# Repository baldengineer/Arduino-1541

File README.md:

# Arduino-1541
Interact with a Commodore 1541 from an Arduino

## Streaming notes
This project was created as a part of a [Bald Engineer Live Stream](https://twitch.tv/baldengineer). For stream-by-stream notes, [check out this repo](https://bald.ee/60-notes).

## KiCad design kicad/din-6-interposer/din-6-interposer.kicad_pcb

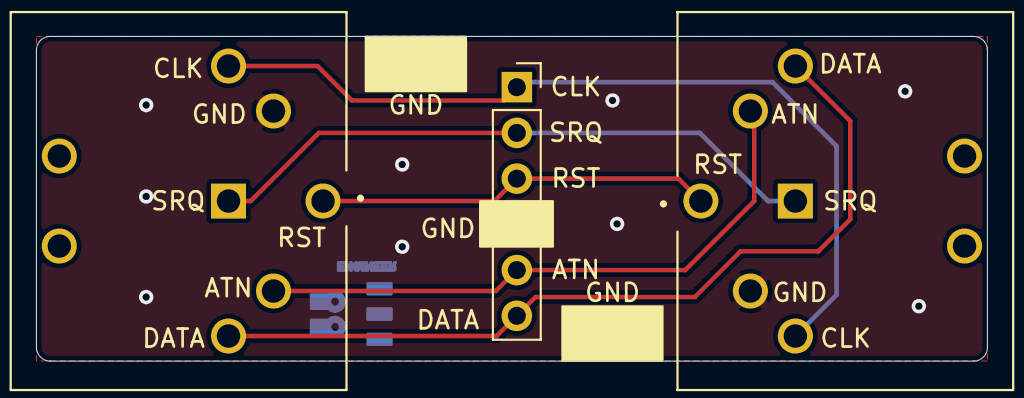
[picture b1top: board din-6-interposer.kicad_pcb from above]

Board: 2 copper layers, 52.8 x 18.0 mm, 6 parts (1 on the bottom side), 6 nets.

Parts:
J1: LA; PinSocket_1x06_P2.54mm_Vertical
J2: IN; CUI_SDF-60J
J3: OUT; CUI_SDF-60J
TP1, TP2: GND; Harwin-S1751-46-Test-Point
svg2mod: G***; BE5v2

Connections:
/ATN: J1.5, J2.3, J3.3
/CLK: J1.1, J2.4, J3.4
/DATA: J1.6, J2.5, J3.5
/RESET: J1.3, J2.6, J3.6
/SRQ: J1.2, J2.1, J3.1
GND: J1.4, J2.2, J3.2, TP1.1, TP2.1

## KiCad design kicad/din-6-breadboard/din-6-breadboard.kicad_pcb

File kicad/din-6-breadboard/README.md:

## DIN 6 (IEC / CBM Bus) Adapter to Breadboard

Contains level shifter to communicate between 3v3 and 5v Arduino boards.

## Streaming notes
This project was created as a part of a [Bald Engineer Live Stream](https://twitch.tv/baldengineer). For stream-by-stream notes, [check out this repo](https://bald.ee/60-notes).

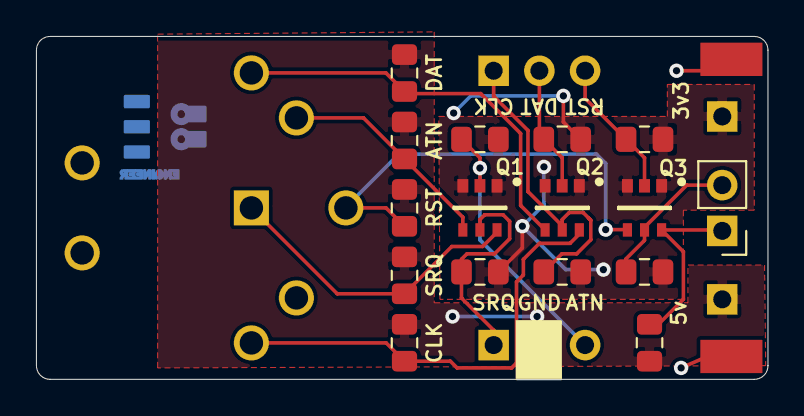
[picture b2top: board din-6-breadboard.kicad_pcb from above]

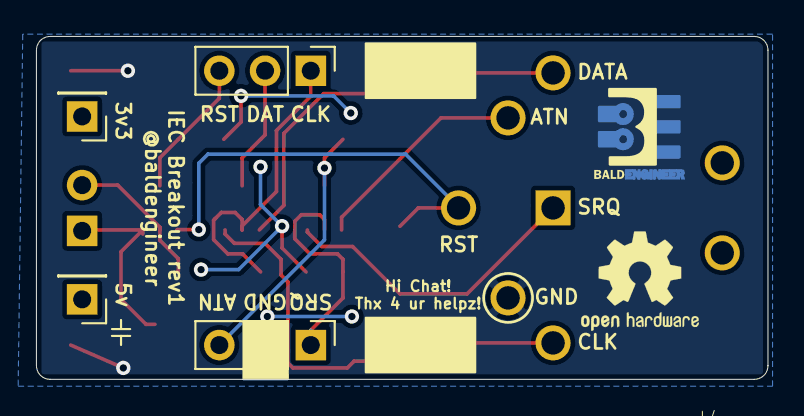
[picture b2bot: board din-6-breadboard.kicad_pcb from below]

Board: 2 copper layers, 40.6 x 19.0 mm, 24 parts (6 on the bottom side), 15 nets.

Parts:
J1, J2: Conn_01x03; PinHeader_1x03_P2.54mm_Vertical
J3: Conn_01x02; PinHeader_1x02_P2.54mm_Vertical
J4: IN; CUI_SDF-60J
J5: 3v3; PinHeader_1x01_P2.54mm_Vertical
J6: 5v; PinHeader_1x01_P2.54mm_Vertical
Q1, Q2, Q3: FDC6301N; ON_Semi-419AG-01-0-0-0
R1, R2, R3, R4, R5, R6, R7, R8, R9, R10, R11, R12: 4k7; R_0805_2012Metric_Pad1.15x1.40mm_HandSolder
TP1, TP2: GND; Harwin-S1751-46-Test-Point
svg2mod: G***; BE5v2

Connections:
+3V3: J5.1, Q1.1, Q1.3, Q2.1, Q2.3, Q3.1, Q3.3, R1.2, R3.2, R5.2, R7.2, R9.2, R11.2
+5V: J6.1, R2.2, R4.2, R6.2, R8.2, R10.2, R12.2
/ATN3: J1.3, Q1.2, R3.1
/ATN5: J4.3, Q1.4, R4.1
/CLK3: J2.1, Q2.5, R5.1
/CLK5: J4.4, Q2.6, R6.1
/DATA3: J2.2, Q2.2, R7.1
/DATA5: J4.5, Q2.4, R8.1
/RESET3: J2.3, Q3.2, R9.1
/RESET5: J4.6, Q3.4, R10.1
/SRQ3: J1.1, Q1.5, R1.1
/SRQ5: J4.1, Q1.6, R2.1
/Spare_Aux_H: J3.1, Q3.6, R12.1
/Spare_Aux_L: J3.2, Q3.5, R11.1
GND: J1.2, J4.2, TP1.1, TP2.1

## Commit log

2021-03-14 pre-routing
2021-03-14 pre-flood 3v and 5v
2021-03-14 breakout r1 ready for fab
2021-03-14 interpose rev1 finish
2021-03-14 create readme for breadbaord adapter
2021-03-14 Create LICENSE
